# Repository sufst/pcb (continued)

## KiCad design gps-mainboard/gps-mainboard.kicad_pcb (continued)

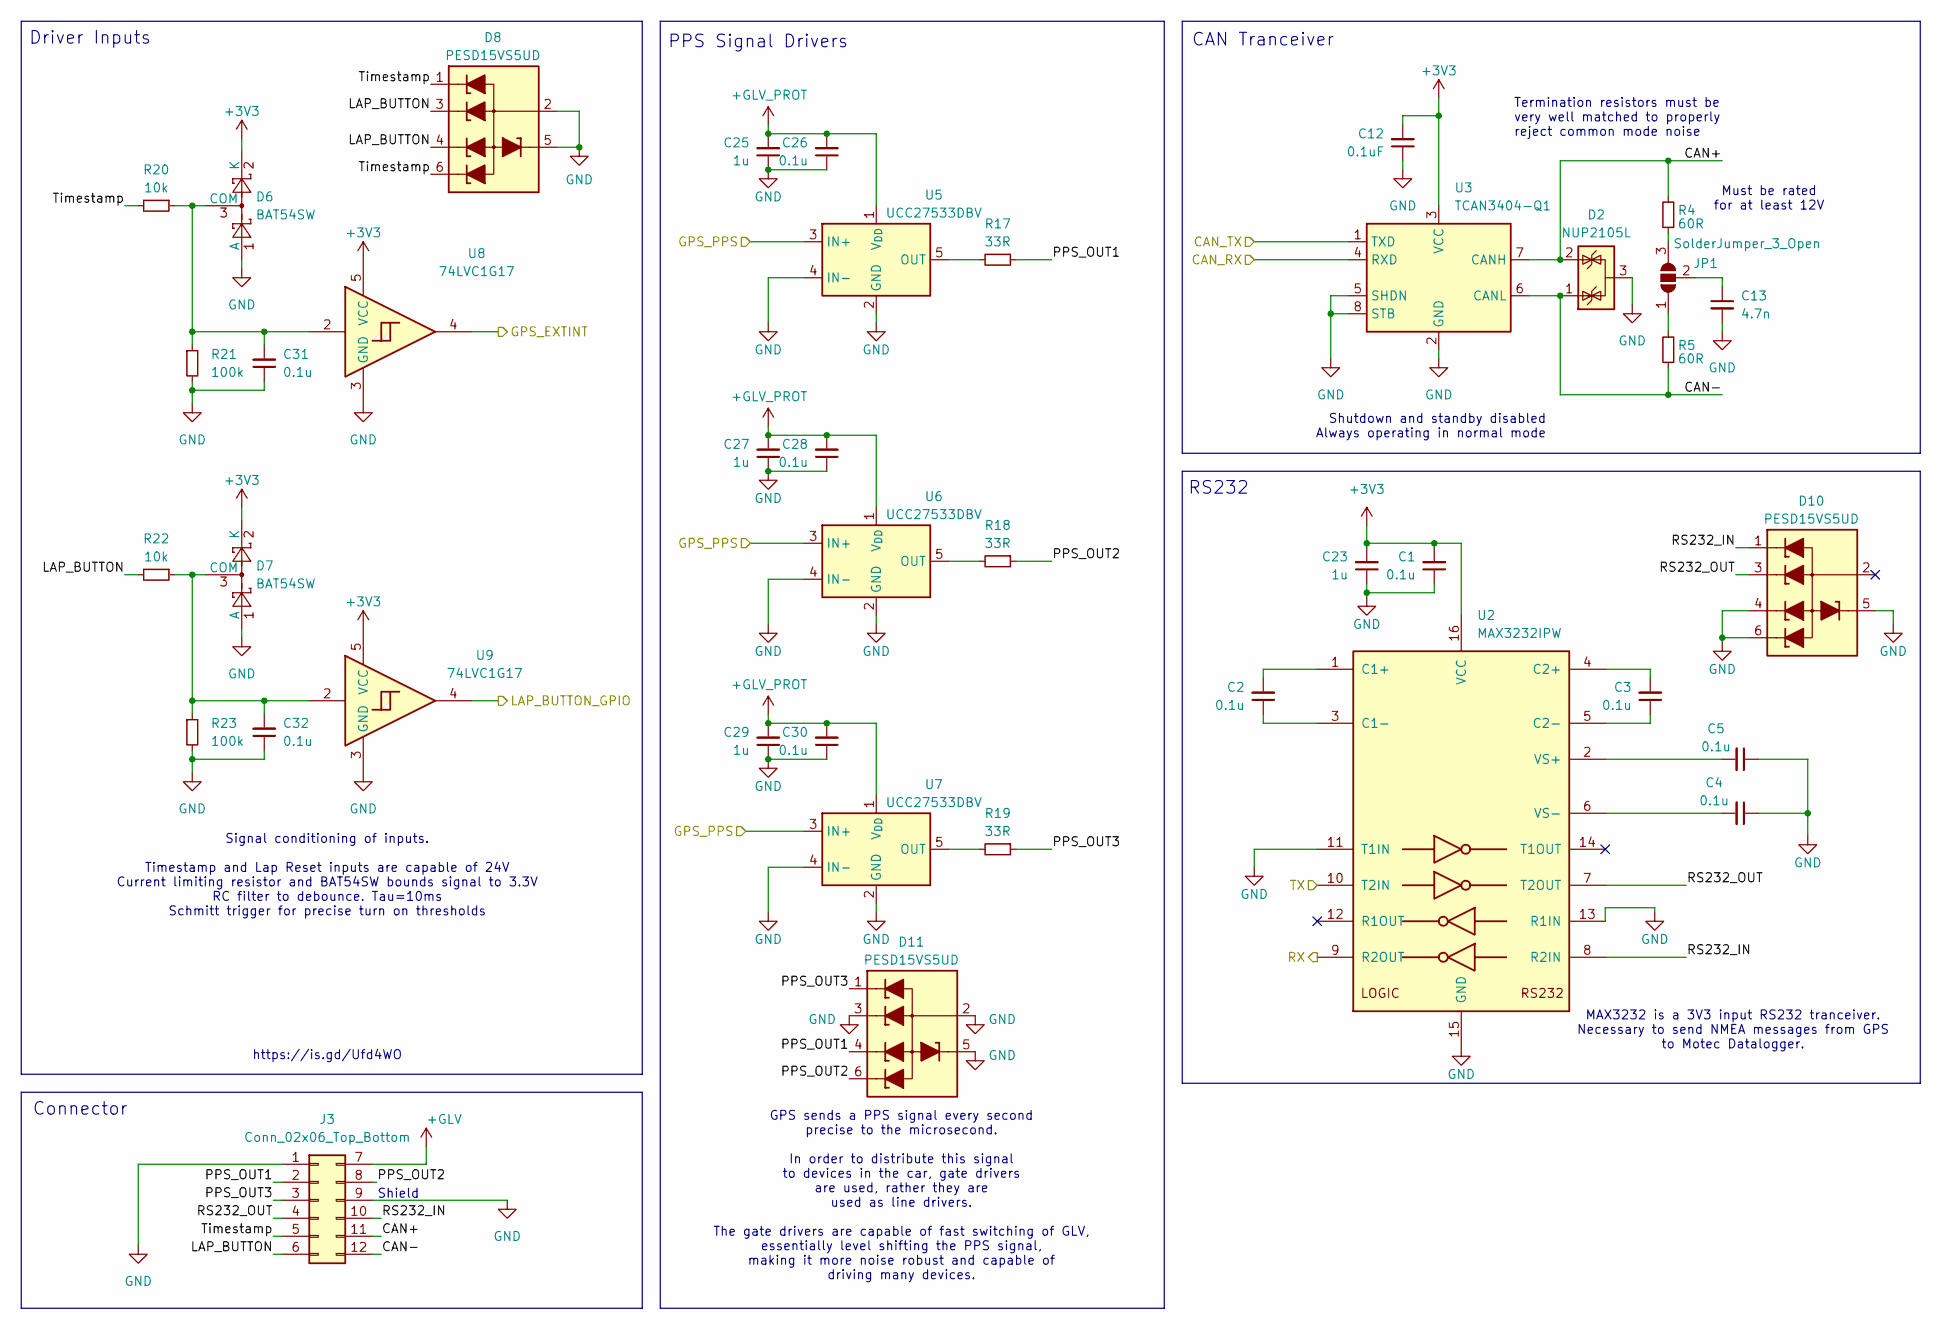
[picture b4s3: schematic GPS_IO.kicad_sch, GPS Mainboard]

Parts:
C1, C2, C3, C4, C5, C26, C28, C30, C31, C32: 0.1u; C_0603_1608Metric_Pad1.08x0.95mm_HandSolder; MPN CL10B104KB85PNL
C12: 0.1uF; C_0603_1608Metric_Pad1.08x0.95mm_HandSolder; MPN CL10B104KB85PNL
C13: 4.7n; C_0603_1608Metric_Pad1.08x0.95mm_HandSolder; MPN 885012206087
C23, C25, C27, C29: 1u; C_0603_1608Metric_Pad1.08x0.95mm_HandSolder; MPN UMK107BJ105KA-T
D2: NUP2105L; SOT-23; MPN NUP2105L
D6, D7: BAT54SW; SOT-323_SC-70_Handsoldering; MPN BAT54SW
D8, D10, D11: PESD15VS5UD; SOT-23-6; MPN PESD15VS5UD
J3: Conn_02x06_Top_Bottom; Molex_Micro-Fit_3.0_43045-1200_2x06_P3.00mm_Horizontal; MPN 43045-1200
JP1: SolderJumper_3_Open; SolderJumper-3_P1.3mm_Open_RoundedPad1.0x1.5mm
R4, R5: 60R; R_0603_1608Metric_Pad0.98x0.95mm_HandSolder; MPN RC0603FR-0760R4L
R17, R18, R19: 33R; R_0603_1608Metric_Pad0.98x0.95mm_HandSolder; MPN RT0603FRE0733RL
R20, R22: 10k; R_0603_1608Metric_Pad0.98x0.95mm_HandSolder; MPN RT0603RF1310KL
R21, R23: 100k; R_0603_1608Metric_Pad0.98x0.95mm_HandSolder; MPN RT0603FRE10100KL
U2: MAX3232IPW; TSSOP-16_4.4x5mm_P0.65mm; MPN MAX3232IPW
U3: TCAN3404-Q1; SOT-23-8_Handsoldering; MPN TCAN3404DDFRQ1
U5, U6, U7: UCC27533DBV; SOT-23-5_HandSoldering; MPN UCC27533DBV
U8, U9: 74LVC1G17; SOT-353_SC-70-5_Handsoldering; MPN 74LVC1G17

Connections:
+3V3: C1.2, C12.2, C23.2, D6.2 (K), D7.2 (K), U2.16 (VCC), U3.3 (VCC), U8.5 (VCC), U9.5 (VCC); also elsewhere on the board
+GLV: J3.7; also elsewhere on the board
+GLV_PROT: C25.2, C26.2, C27.2, C28.2, C29.2, C30.2, U5.1 (V_{DD}), U6.1 (V_{DD}), U7.1 (V_{DD}); also elsewhere on the board
/CAN_RX: U3.4 (RXD); also elsewhere on the board
/CAN_TX: U3.1 (TXD); also elsewhere on the board
/GPS_EXTINT: U8.4; also elsewhere on the board
/GPS_IO/CAN+: D2.2 (K), J3.11, R4.2, U3.7 (CANH)
/GPS_IO/CAN-: D2.1 (K), J3.12, R5.1, U3.6 (CANL)
/GPS_IO/LAP_BUTTON: D8.3 (L2), D8.4 (L3), J3.6, R22.2
/GPS_IO/PPS_OUT1: D11.4 (L3), J3.2, R17.1
/GPS_IO/PPS_OUT2: D11.6 (L4), J3.8, R18.1
/GPS_IO/PPS_OUT3: D11.1 (L1), J3.3, R19.1
/GPS_IO/RS232_IN: D10.1 (L1), J3.10, U2.8 (R2IN)
/GPS_IO/RS232_OUT: D10.3 (L2), J3.4, U2.7 (T2OUT)
/GPS_IO/Timestamp: D8.1 (L1), D8.6 (L4), J3.5, R20.2
/GPS_PPS: U5.3 (IN+), U6.3 (IN+), U7.3 (IN+); also elsewhere on the board
/LAP_BUTTON: U9.4; also elsewhere on the board
/OFFBOARD_UART_IN: U2.9 (R2OUT); also elsewhere on the board
/OFFBOARD_UART_OUT: U2.10 (T2IN); also elsewhere on the board
GND: C1.1, C4.1, C5.1, C12.1, C13.2, C23.1, C25.1, C26.1, C27.1, C28.1, C29.1, C30.1, C31.1, C32.1, D2.3 (A), D6.1 (A), D7.1 (A), D8.2 (VN), D8.5 (VN), D10.4 (L3), D10.5 (VN), D10.6 (L4), D11.2 (VN), D11.3 (L2), D11.5 (VN), J3.1, J3.9, R21.2, R23.2, U2.11 (T1IN), U2.13 (R1IN), U2.15 (GND), U3.2 (GND), U3.5 (SHDN), U3.8 (STB), U5.2 (GND), U5.4 (IN-), U6.2 (GND), U6.4 (IN-), U7.2 (GND), U7.4 (IN-), U8.3 (GND), U9.3 (GND); also elsewhere on the board
unnamed: C31.2, D6.3 (COM), R20.1, R21.1, U8.2
unnamed: C32.2, D7.3 (COM), R22.1, R23.1, U9.2
unnamed: JP1.1 (A), R5.2
unnamed: JP1.3 (B), R4.1
unnamed: C13.1, JP1.2 (C)
unnamed: C2.2, U2.1 (C1+)
unnamed: C2.1, U2.3 (C1-)
unnamed: C3.2, U2.4 (C2+)
unnamed: C3.1, U2.5 (C2-)
unnamed: C5.2, U2.2 (VS+)
unnamed: C4.2, U2.6 (VS-)
unnamed: R17.2, U5.5 (OUT)
unnamed: R18.2, U6.5 (OUT)
unnamed: R19.2, U7.5 (OUT)

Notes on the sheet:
Driver Inputs
https://is.gd/Ufd4WO
Shutdown and standby disabled Always operating in normal mode
GPS sends a PPS signal every second precise to the microsecond. In order to distribute this signal to devices in the car, gate drivers are used, rather they are used as line drivers. The gate drivers are capable of fast switching of GLV, essentially level shifting the PPS signal, making it more noi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
Must be rated for at least 12V
Connector
RS232
MAX3232 is a 3V3 input RS232 tranceiver. Necessary to send NMEA messages from GPS to Motec Datalogger.
PPS Signal Drivers
Signal conditioning of inputs. Timestamp and Lap Reset inputs are capable of 24V Current limiting resistor and BAT54SW bounds signal to 3.3V RC filter to debounce. Tau=10ms Schmitt trigger for precise turn on thresholds
CAN Tranceiver
Shield
Termination resistors must be very well matched to properly reject common mode noise

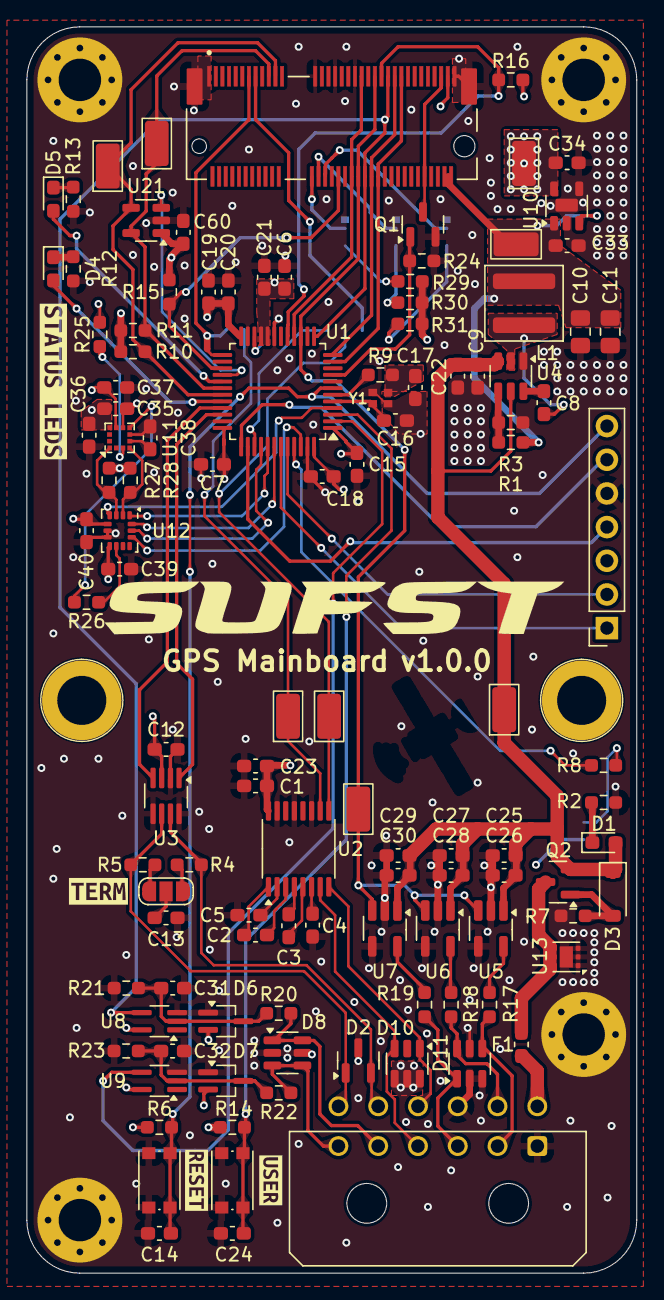
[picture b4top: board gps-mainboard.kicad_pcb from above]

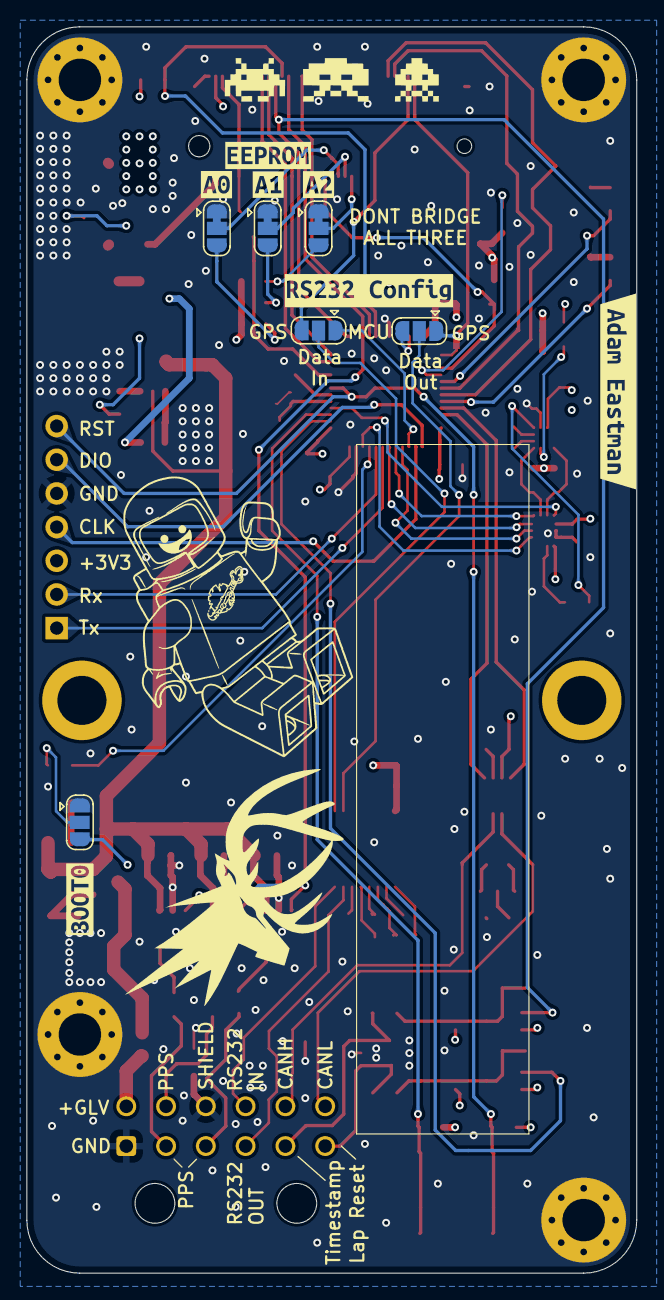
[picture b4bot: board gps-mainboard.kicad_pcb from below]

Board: 4 copper layers, 46.0 x 94.0 mm, 139 parts (13 on the bottom side), 88 nets.

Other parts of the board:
kibuzzard-69CC78BA: G***; kibuzzard-69CC78BA
kibuzzard-69CC717E: G***; kibuzzard-69CC717E
kibuzzard-69CC718B: G***; kibuzzard-69CC718B
kibuzzard-69CC780C: G***; kibuzzard-69CC780C
kibuzzard-69CC784C: G***; kibuzzard-69CC784C
kibuzzard-69CC7130: G***; kibuzzard-69CC7130
kibuzzard-69CC7837: G***; kibuzzard-69CC7837
kibuzzard-69CC7843: G***; kibuzzard-69CC7843
kibuzzard-69CD1CA6: G***; kibuzzard-69CD1CA6
kibuzzard-69CD28D6: G***; kibuzzard-69CD28D6
kibuzzard-69D03494: G***; kibuzzard-69D03494

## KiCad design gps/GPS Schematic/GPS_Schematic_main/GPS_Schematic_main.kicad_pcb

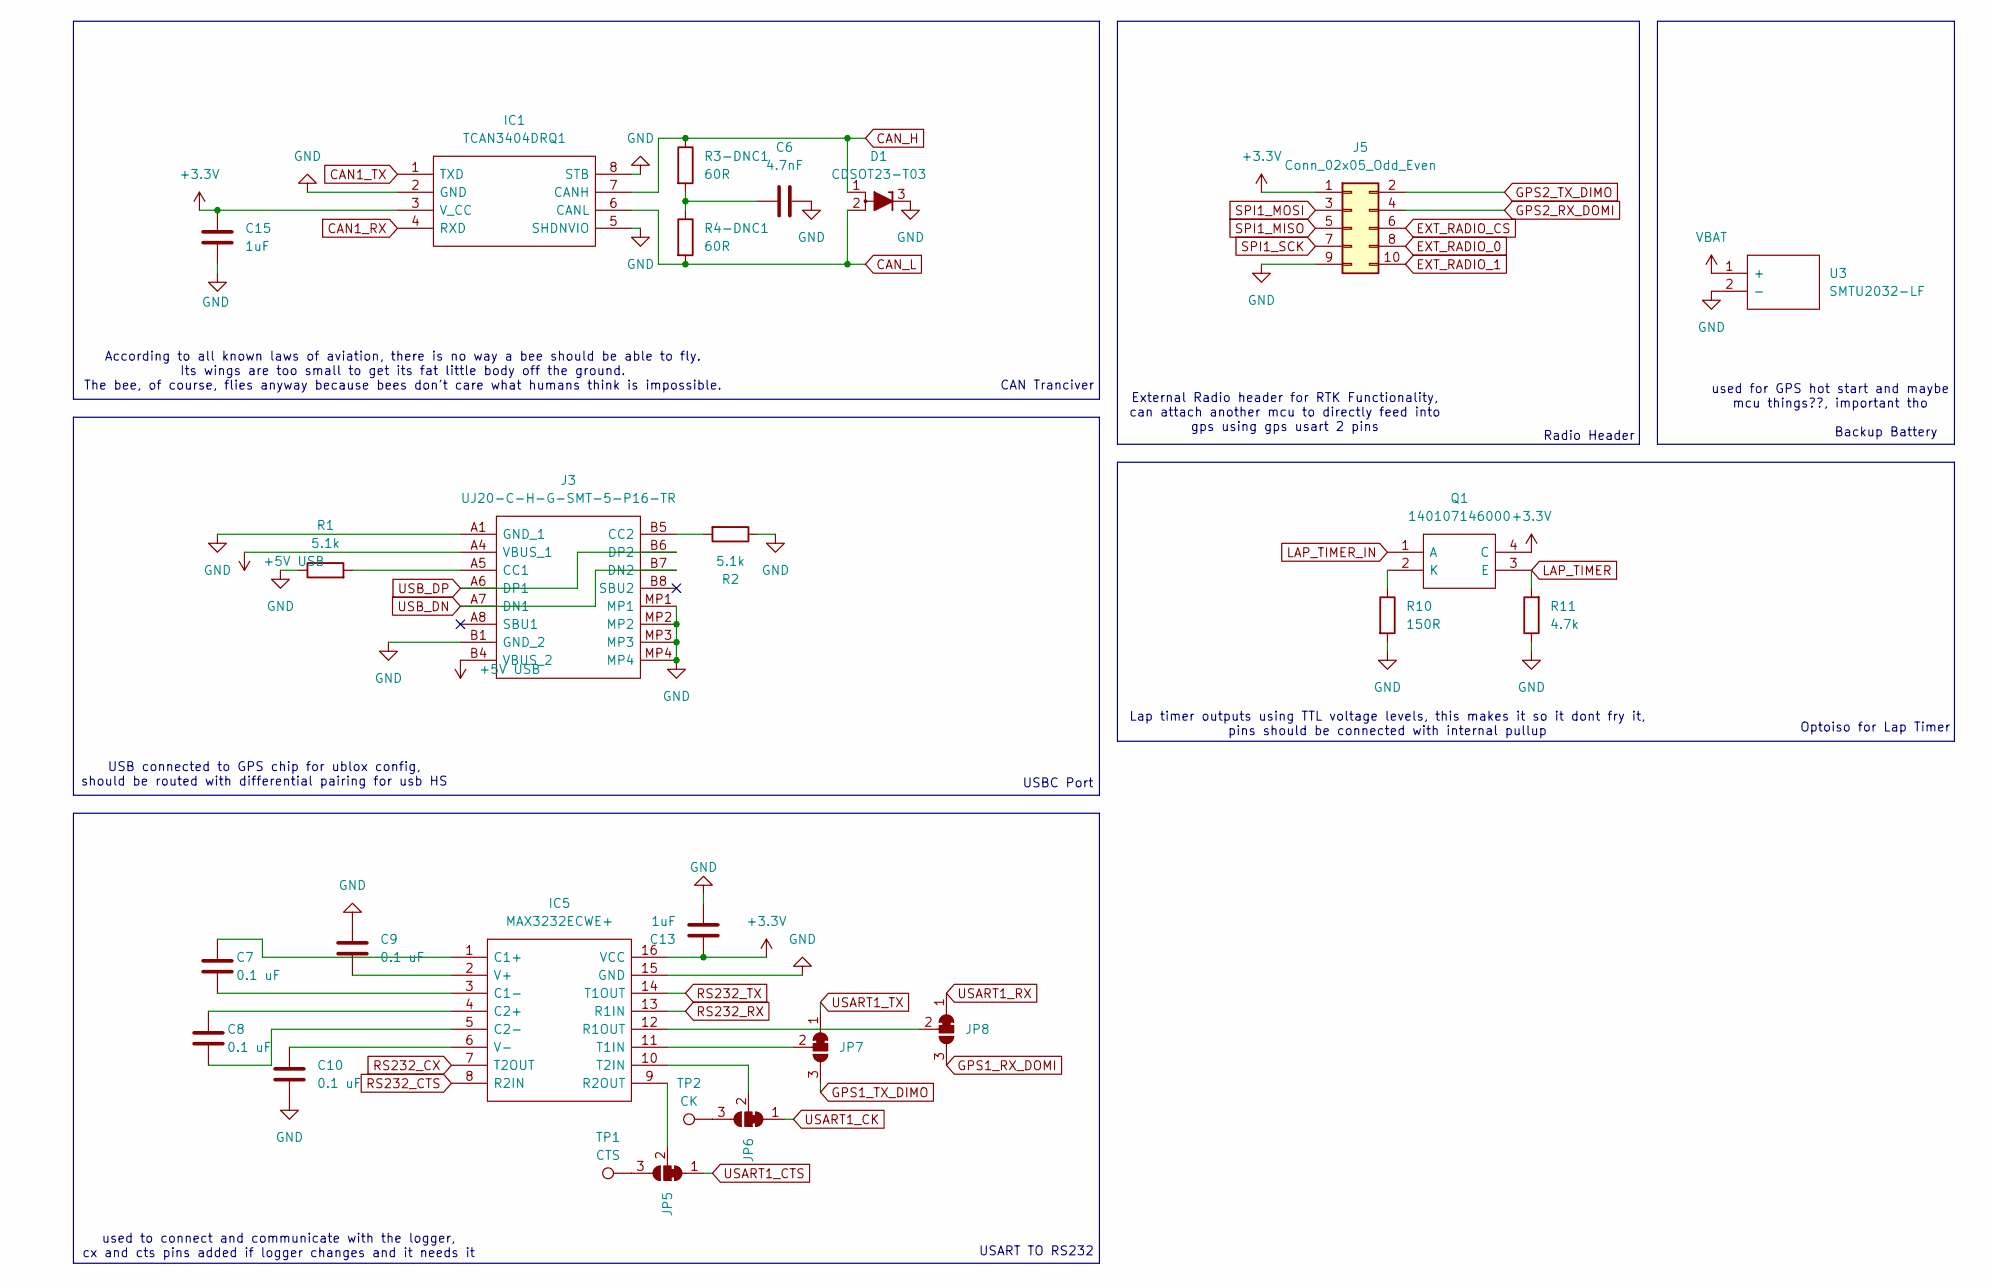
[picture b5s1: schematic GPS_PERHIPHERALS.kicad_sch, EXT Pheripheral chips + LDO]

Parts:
C6: 4.7nF; C_0805_2012Metric
C7, C8, C9, C10: 0.1 uF; C_0805_2012Metric
C13, C15: 1uF; C_0805_2012Metric
D1: CDSOT23-T03; SOT-23
IC1: TCAN3404DRQ1; SOIC127P600X175-8N; Mouser Part Number 595-TCAN3404DRQ1
IC5: MAX3232ECWE+; SOIC127P1032X265-16N; Mouser Part Number 700-MAX3232ECWE
J3: UJ20-C-H-G-SMT-5-P16-TR; UJ20CHGSMT5P16TR; Mouser Part Number 179-UJ20CHGSMT5P16TR
J5: Conn_02x05_Odd_Even; PinHeader_2x05_P2.54mm_Vertical
JP5, JP6, JP7, JP8: SolderJumper_3_Bridged12; SolderJumper-3_P1.3mm_Bridged12_RoundedPad1.0x1.5mm
Q1: 140107146000; Mouser Part Number 710-140107146000
R1, R2: 5.1k; R_0805_2012Metric
R3-DNC1, R4-DNC1: 60R; R_0805_2012Metric_Pad1.15x1.40mm_HandSolder
R10: 150R; R_0805_2012Metric
R11: 4.7k; R_0805_2012Metric
TP1: CTS; TestPoint_Pad_D1.0mm
TP2: CK; TestPoint_Pad_D1.0mm
U3: SMTU2032-LF; SMTU2032LF; Mouser Part Number 614-SMTU2032-LF

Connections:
+3.3V: C13.1, C15.1, IC1.3 (V_CC), IC5.16 (VCC), J5.1, Q1.4 (C); also elsewhere on the board
+5V USB: J3.A4 (VBUS_1), J3.B4 (VBUS_2); also elsewhere on the board
CAN1_RX: IC1.4 (RXD); also elsewhere on the board
CAN1_TX: IC1.1 (TXD); also elsewhere on the board
CAN_H: D1.1 (A), IC1.7 (CANH), R3-DNC1.1; also elsewhere on the board
CAN_L: D1.2 (A), IC1.6 (CANL), R4-DNC1.2; also elsewhere on the board
EXT_RADIO_0: J5.8; also elsewhere on the board
EXT_RADIO_1: J5.10; also elsewhere on the board
EXT_RADIO_CS: J5.6; also elsewhere on the board
GND: C6.2, C9.1, C10.2, C13.2, C15.2, D1.3 (K), IC1.2 (GND), IC1.5 (SHDNVIO), IC1.8 (STB), IC5.15 (GND), J3.A1 (GND_1), J3.B1 (GND_2), J3.MP1, J3.MP2, J3.MP3, J3.MP4, J5.9, R1.1, R2.1, R10.2, R11.1, U3.2 (-); also elsewhere on the board
GPS1_RX_DOMI: JP8.3 (B); also elsewhere on the board
GPS1_TX_DIMO: JP7.3 (B); also elsewhere on the board
GPS2_RX_DOMI: J5.4; also elsewhere on the board
GPS2_TX_DIMO: J5.2; also elsewhere on the board
LAP_TIMER: Q1.3 (E), R11.2; also elsewhere on the board
LAP_TIMER_IN: Q1.1 (A); also elsewhere on the board
unnamed: C6.1, R3-DNC1.2, R4-DNC1.1
unnamed: C7.1, IC5.1 (C1+)
unnamed: C7.2, IC5.3 (C1-)
unnamed: C8.1, IC5.4 (C2+)
unnamed: C8.2, IC5.5 (C2-)
unnamed: IC5.12 (R1OUT), JP8.2 (C)
unnamed: IC5.9 (R2OUT), JP5.2 (C)
unnamed: IC5.11 (T1IN), JP7.2 (C)
unnamed: IC5.10 (T2IN), JP6.2 (C)
unnamed: C9.2, IC5.2 (V+)
unnamed: C10.1, IC5.6 (V-)
unnamed: J3.A5 (CC1), R1.2
unnamed: J3.B5 (CC2), R2.2
unnamed 63: JP5.3 (B), TP1.1; also elsewhere on the board
unnamed 64: JP6.3 (B), TP2.1; also elsewhere on the board
unnamed: Q1.2 (K), R10.1
RS232_CTS: IC5.8 (R2IN); also elsewhere on the board
RS232_CX: IC5.7 (T2OUT); also elsewhere on the board
RS232_RX: IC5.13 (R1IN); also elsewhere on the board
RS232_TX: IC5.14 (T1OUT); also elsewhere on the board
SPI1_MISO: J5.5; also elsewhere on the board
SPI1_MOSI: J5.3; also elsewhere on the board
SPI1_SCK: J5.7; also elsewhere on the board
USART1_CK: JP6.1 (A); also elsewhere on the board
USART1_CTS: JP5.1 (A); also elsewhere on the board
USART1_RX: JP8.1 (A); also elsewhere on the board
USART1_TX: JP7.1 (A); also elsewhere on the board
USB_DN: J3.A7 (DN1), J3.B7 (DN2); also elsewhere on the board
USB_DP: J3.A6 (DP1), J3.B6 (DP2); also elsewhere on the board
VBAT: U3.1 (+); also elsewhere on the board

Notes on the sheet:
External Radio header for RTK Functionality, can attach another mcu to directly feed into gps using gps usart 2 pins
Radio Header
Optoiso for Lap Timer
Backup Battery
According to all known laws of aviation, there is no way a bee should be able to fly. Its wings are too small to get its fat little body off the ground. The bee, of course, flies anyway because bees don't care what humans think is impossible.
USART TO RS232
USB connected to GPS chip for ublox config, should be routed with differential pairing for usb HS
used to connect and communicate with the logger, cx and cts pins added if logger changes and it needs it
CAN Tranciver
USBC Port
used for GPS hot start and maybe mcu things??, important tho
Lap timer outputs using TTL voltage levels, this makes it so it dont fry it, pins should be connected with internal pullup

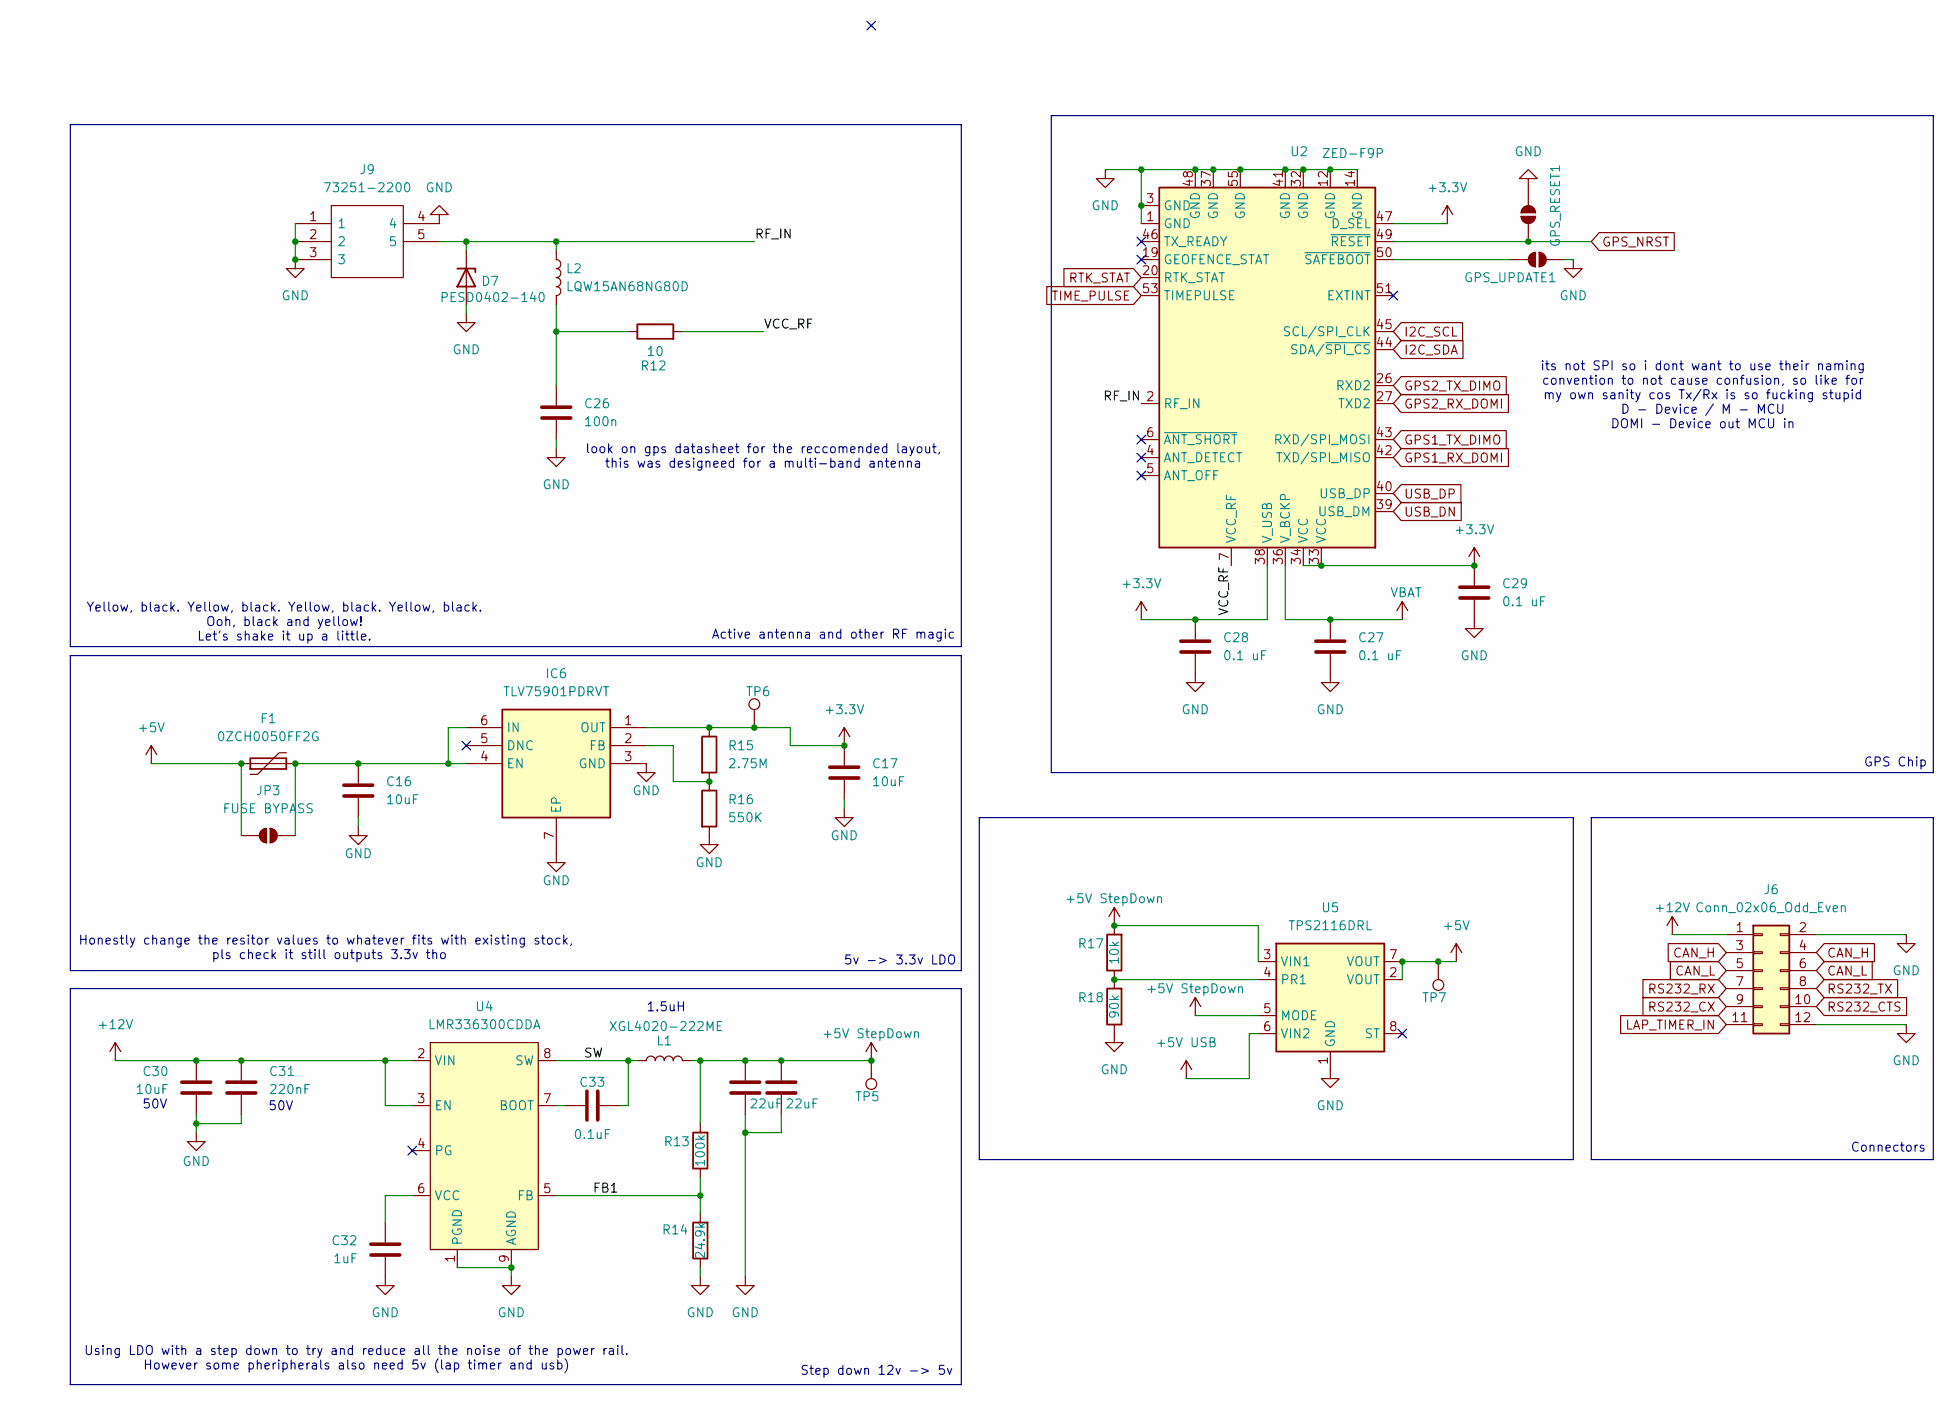
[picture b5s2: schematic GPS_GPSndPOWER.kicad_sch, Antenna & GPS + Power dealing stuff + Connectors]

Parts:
C16, C17, C30: 10uF; C_0805_2012Metric
C26: 100n; C_0805_2012Metric
C27, C28, C29: 0.1 uF; C_0805_2012Metric
C31: 220nF; C_0805_2012Metric
C32: 1uF; C_0805_2012Metric
C33: 0.1uF; C_0805_2012Metric
C34, C35: 22uF; C_0805_2012Metric
D7: PESD0402-140; D_01005_0402Metric_Pad0.57x0.30mm_HandSolder
F1: 0ZCH0050FF2G; Fuse_1210_3225Metric_Pad1.42x2.65mm_HandSolder
GPS_RESET1: SolderJumper_2_Open; SolderJumper-2_P1.3mm_Open_RoundedPad1.0x1.5mm
GPS_UPDATE1: SolderJumper_2_Open; SolderJumper-2_P1.3mm_Open_RoundedPad1.0x1.5mm
IC6: TLV75901PDRVT; SON65P200X200X80-7N; Mouser Part Number 595-TLV75901PDRVT
J6: Conn_02x06_Odd_Even; Molex_Micro-Fit_3.0_43045-1200_2x06_P3.00mm_Horizontal
J9: 73251-2200; Mouser Part Number 538-73251-2200
JP3: FUSE BYPASS; SolderJumper-2_P1.3mm_Open_RoundedPad1.0x1.5mm
L1: XGL4020-222ME; L_Coilcraft_XxL4020
L2: LQW15AN68NG80D; D_01005_0402Metric_Pad0.57x0.30mm_HandSolder
R12: 10; R_0805_2012Metric
R13: 100k; R_0805_2012Metric
R14: 24.9k; R_0805_2012Metric
R15: 2.75M; R_0805_2012Metric
R16: 550K; R_0805_2012Metric
R17: 10k; R_0805_2012Metric
R18: 90k; R_0805_2012Metric
TP5, TP6, TP7: TestPoint; TestPoint_Pad_D1.5mm
U2: ZED-F9P; ublox_ZED
U4: LMR336300CDDA; Texas_R-PDSO-G8_EP2.95x4.9mm_Mask2.4x3.1mm
U5: TPS2116DRL; SOT-583-8

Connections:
+3.3V: C17.1, C28.1, C29.1, IC6.1 (OUT), R15.1, TP6.1, U2.33 (VCC), U2.34 (VCC), U2.38 (V_USB), U2.47 (D_SEL); also elsewhere on the board
+5V: F1.1, JP3.1 (A), TP7.1, U5.2 (VOUT), U5.7 (VOUT); also elsewhere on the board
+5V StepDown: C34.1, C35.1, L1.2, R13.2, R17.2, TP5.1, U5.3 (VIN1), U5.5 (MODE); also elsewhere on the board
+5V USB: U5.6 (VIN2); also elsewhere on the board
+12V: C30.1, C31.1, J6.1, U4.2 (VIN), U4.3 (EN)
/GPS and Antenna/FB1: R13.1, R14.2, U4.5 (FB)
/GPS and Antenna/RF_IN: D7.1 (K), J9.5, L2.1, U2.2 (RF_IN)
/GPS and Antenna/SW: C33.2, L1.1, U4.8 (SW)
/GPS and Antenna/VCC_RF: R12.2, U2.7 (VCC_RF)
CAN_H: J6.3, J6.4; also elsewhere on the board
CAN_L: J6.5, J6.6; also elsewhere on the board
GND: C16.2, C17.2, C26.1, C27.2, C28.2, C29.2, C30.2, C31.2, C32.2, C34.2, C35.2, D7.2 (A), GPS_RESET1.1 (A), GPS_UPDATE1.1 (A), IC6.3 (GND), IC6.7 (EP), J6.2, J6.12, J9.1, J9.2, J9.3, J9.4, R14.1, R16.2, R18.1, U2.1 (GND), U2.3 (GND), U2.12 (GND), U2.14 (GND), U2.32 (GND), U2.37 (GND), U2.41 (GND), U2.48 (GND), U2.55 (GND), U4.1 (PGND), U4.9 (AGND), U5.1 (GND); also elsewhere on the board
GPS1_RX_DOMI: U2.42 (TXD/SPI_MISO); also elsewhere on the board
GPS1_TX_DIMO: U2.43 (RXD/SPI_MOSI); also elsewhere on the board
GPS2_RX_DOMI: U2.27 (TXD2); also elsewhere on the board
GPS2_TX_DIMO: U2.26 (RXD2); also elsewhere on the board
GPS_NRST: GPS_RESET1.2 (B), U2.49 (~RESET); also elsewhere on the board
I2C_SCL: U2.45 (SCL/SPI_CLK); also elsewhere on the board
I2C_SDA: U2.44 (SDA/~SPI_CS); also elsewhere on the board
LAP_TIMER_IN: J6.11; also elsewhere on the board
unnamed: C26.2, L2.2, R12.1
unnamed 45: GPS_UPDATE1.2 (B), U2.50 (~SAFEBOOT); also elsewhere on the board
unnamed 58: C16.1, F1.2, IC6.4 (EN), IC6.6 (IN), JP3.2 (B); also elsewhere on the board
unnamed: IC6.2 (FB), R15.2, R16.1
unnamed: C33.1, U4.7 (BOOT)
unnamed: C32.1, U4.6 (VCC)
unnamed: R17.1, R18.2, U5.4 (PR1)
RS232_CTS: J6.10; also elsewhere on the board
RS232_CX: J6.9; also elsewhere on the board
RS232_RX: J6.7; also elsewhere on the board
RS232_TX: J6.8; also elsewhere on the board
RTK_STAT: U2.20 (RTK_STAT); also elsewhere on the board
TIME_PULSE: U2.53 (TIMEPULSE); also elsewhere on the board
USB_DN: U2.39 (USB_DM); also elsewhere on the board
USB_DP: U2.40 (USB_DP); also elsewhere on the board
VBAT: C27.1, U2.36 (V_BCKP); also elsewhere on the board

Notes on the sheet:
Honestly change the resitor values to whatever fits with existing stock, pls check it still outputs 3.3v tho
look on gps datasheet for the reccomended layout, this was designeed for a multi-band antenna
1.5uH
50V
5v -> 3.3v LDO
Active antenna and other RF magic
Connectors
GPS Chip
Yellow, black. Yellow, black. Yellow, black. Yellow, black. Ooh, black and yellow! Let's shake it up a little.
Step down 12v -> 5v
Using LDO with a step down to try and reduce all the noise of the power rail. However some pheripherals also need 5v (lap timer and usb)
its not SPI so i dont want to use their naming convention to not cause confusion, so like for my own sanity cos Tx/Rx is so fucking stupid D - Device / M - MCU DOMI - Device out MCU in

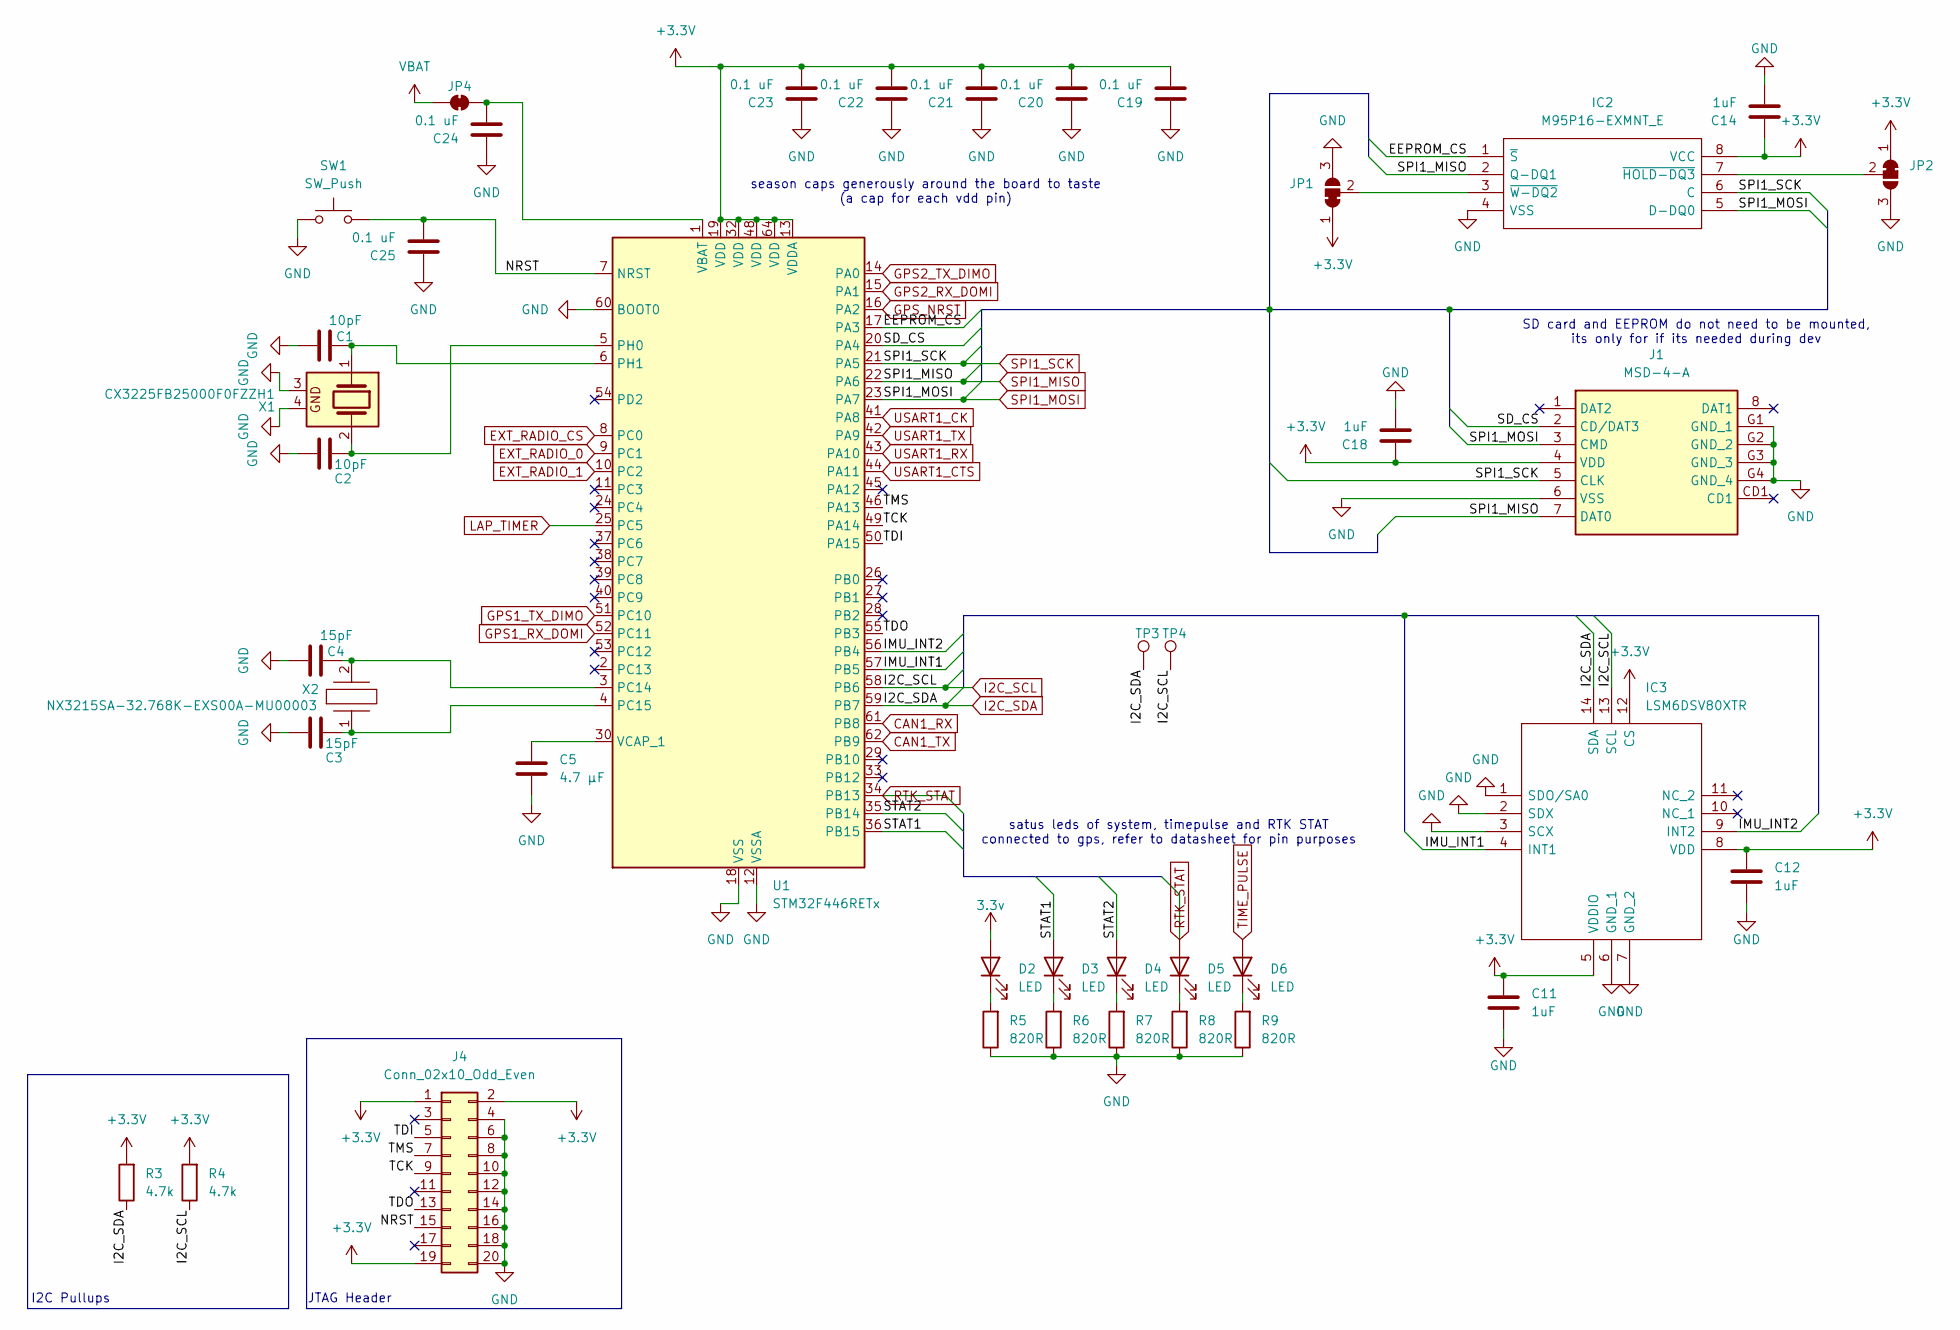
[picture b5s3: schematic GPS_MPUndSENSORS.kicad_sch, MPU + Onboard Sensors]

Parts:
C1, C2: 10pF; C_0805_2012Metric
C3, C4: 15pF; C_0805_2012Metric
C5: 4.7 µF; C_0805_2012Metric
C11, C12, C14, C18: 1uF; C_0805_2012Metric
C19, C20, C21, C22, C23, C24, C25: 0.1 uF; C_0805_2012Metric
D2, D3, D4, D5, D6: LED; LED_0201_0603Metric
IC2: M95P16-EXMNT_E; SOIC127P600X175-8N; Mouser Part Number 511-M95P16-EXMNT/E
IC3: LSM6DSV80XTR; LSM6DSV16BXTR; Manufacturer_Part_Number LSM6DSV80XTR
J1: MSD-4-A; MSD4A; Mouser Part Number 179-MSD-4-A
J4: Conn_02x10_Odd_Even; PinHeader_2x10_P2.54mm_Vertical
JP1, JP2: SolderJumper_3_Bridged12; SolderJumper-3_P1.3mm_Bridged12_RoundedPad1.0x1.5mm
JP4: SolderJumper_2_Bridged; SolderJumper-2_P1.3mm_Bridged_RoundedPad1.0x1.5mm
R3, R4: 4.7k; R_0805_2012Metric
R5, R6, R7, R8, R9: 820R; R_0805_2012Metric
SW1: SW_Push; SW_PUSH_6mm_H4.3mm
TP3, TP4: TestPoint; TestPoint_Pad_D1.5mm
U1: STM32F446RETx; LQFP-64_10x10mm_P0.5mm
X1: CX3225FB25000F0FZZH1
X2: NX3215SA-32.768K-EXS00A-MU00003; NX3215SA32768KEXS00AMU00003; Mouser Part Number 344-NX3215SA32.768K3

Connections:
3.3v: D2.2 (A)
+3.3V: C11.1, C12.1, C14.1, C18.1, C19.2, C20.2, C21.2, C22.2, C23.2, IC2.8 (VCC), IC3.5 (VDDIO), IC3.8 (VDD), IC3.12 (CS), J1.4 (VDD), J4.1, J4.2, J4.19, JP1.1 (A), JP2.1 (A), R3.2, R4.2, U1.13 (VDDA), U1.19 (VDD), U1.32 (VDD), U1.48 (VDD), U1.64 (VDD); also elsewhere on the board
/MPU/EEPROM_CS: IC2.1 (~S), U1.17 (PA3)
/MPU/IMU_INT1: IC3.4 (INT1), U1.57 (PB5)
/MPU/IMU_INT2: IC3.9 (INT2), U1.56 (PB4)
/MPU/NRST: C25.2, J4.15, SW1.2, U1.7 (NRST)
/MPU/SD_CS: J1.2 (CD/DAT3), U1.20 (PA4)
/MPU/STAT1: D3.2 (A), U1.36 (PB15)
/MPU/STAT2: D4.2 (A), U1.35 (PB14)
/MPU/TCK: J4.9, U1.49 (PA14)
/MPU/TDI: J4.5, U1.50 (PA15)
/MPU/TDO: J4.13, U1.55 (PB3)
/MPU/TMS: J4.7, U1.46 (PA13)
CAN1_RX: U1.61 (PB8); also elsewhere on the board
CAN1_TX: U1.62 (PB9); also elsewhere on the board
EXT_RADIO_0: U1.9 (PC1); also elsewhere on the board
EXT_RADIO_1: U1.10 (PC2); also elsewhere on the board
EXT_RADIO_CS: U1.8 (PC0); also elsewhere on the board
GND: C1.2, C2.2, C3.2, C4.2, C5.2, C11.2, C12.2, C14.2, C18.2, C19.1, C20.1, C21.1, C22.1, C23.1, C24.1, C25.1, IC2.4 (VSS), IC3.1 (SDO/SA0), IC3.2 (SDX), IC3.3 (SCX), IC3.6 (GND_1), IC3.7 (GND_2), J1.6 (VSS), J1.G1 (GND_1), J1.G2 (GND_2), J1.G3 (GND_3), J1.G4 (GND_4), J4.4, J4.6, J4.8, J4.10, J4.12, J4.14, J4.16, J4.18, J4.20, JP1.3 (B), JP2.3 (B), R5.1, R6.1, R7.1, R8.1, R9.1, SW1.1, U1.12 (VSSA), U1.18 (VSS), U1.31 (VSS), U1.47 (VSS), U1.60 (BOOT0), U1.63 (VSS), X1.3, X1.4; also elsewhere on the board
GPS1_RX_DOMI: U1.52 (PC11); also elsewhere on the board
GPS1_TX_DIMO: U1.51 (PC10); also elsewhere on the board
GPS2_RX_DOMI: U1.15 (PA1); also elsewhere on the board
GPS2_TX_DIMO: U1.14 (PA0); also elsewhere on the board
GPS_NRST: U1.16 (PA2); also elsewhere on the board
I2C_SCL: IC3.13 (SCL), R4.1, TP4.1, U1.58 (PB6); also elsewhere on the board
I2C_SDA: IC3.14 (SDA), R3.1, TP3.1, U1.59 (PB7); also elsewhere on the board
LAP_TIMER: U1.25 (PC5); also elsewhere on the board
unnamed: D2.1 (K), R5.2
unnamed: D3.1 (K), R6.2
unnamed: D4.1 (K), R7.2
unnamed: D5.1 (K), R8.2
unnamed: D6.1 (K), R9.2
unnamed: IC2.7 (~HOLD-DQ3), JP2.2 (C)
unnamed: IC2.3 (~W-DQ2), JP1.2 (C)
unnamed: C24.2, JP4.2 (B), U1.1 (VBAT)
unnamed: C4.1, U1.3 (PC14), X2.2
unnamed: C3.1, U1.4 (PC15), X2.1
unnamed: C2.1, U1.5 (PH0), X1.2
unnamed: C1.1, U1.6 (PH1), X1.1
unnamed: C5.1, U1.30 (VCAP_1)
RTK_STAT: D5.2 (A), U1.34 (PB13); also elsewhere on the board
SPI1_MISO: IC2.2 (Q-DQ1), J1.7 (DAT0), U1.22 (PA6); also elsewhere on the board
SPI1_MOSI: IC2.5 (D-DQ0), J1.3 (CMD), U1.23 (PA7); also elsewhere on the board
SPI1_SCK: IC2.6 (C), J1.5 (CLK), U1.21 (PA5); also elsewhere on the board
TIME_PULSE: D6.2 (A); also elsewhere on the board
USART1_CK: U1.41 (PA8); also elsewhere on the board
USART1_CTS: U1.44 (PA11); also elsewhere on the board
USART1_RX: U1.43 (PA10); also elsewhere on the board
USART1_TX: U1.42 (PA9); also elsewhere on the board
VBAT: JP4.1 (A); also elsewhere on the board

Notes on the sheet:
SD card and EEPROM do not need to be mounted, its only for if its needed during dev
satus leds of system, timepulse and RTK STAT connected to gps, refer to datasheet for pin purposes
season caps generously around the board to taste (a cap for each vdd pin)
JTAG Header
I2C Pullups
